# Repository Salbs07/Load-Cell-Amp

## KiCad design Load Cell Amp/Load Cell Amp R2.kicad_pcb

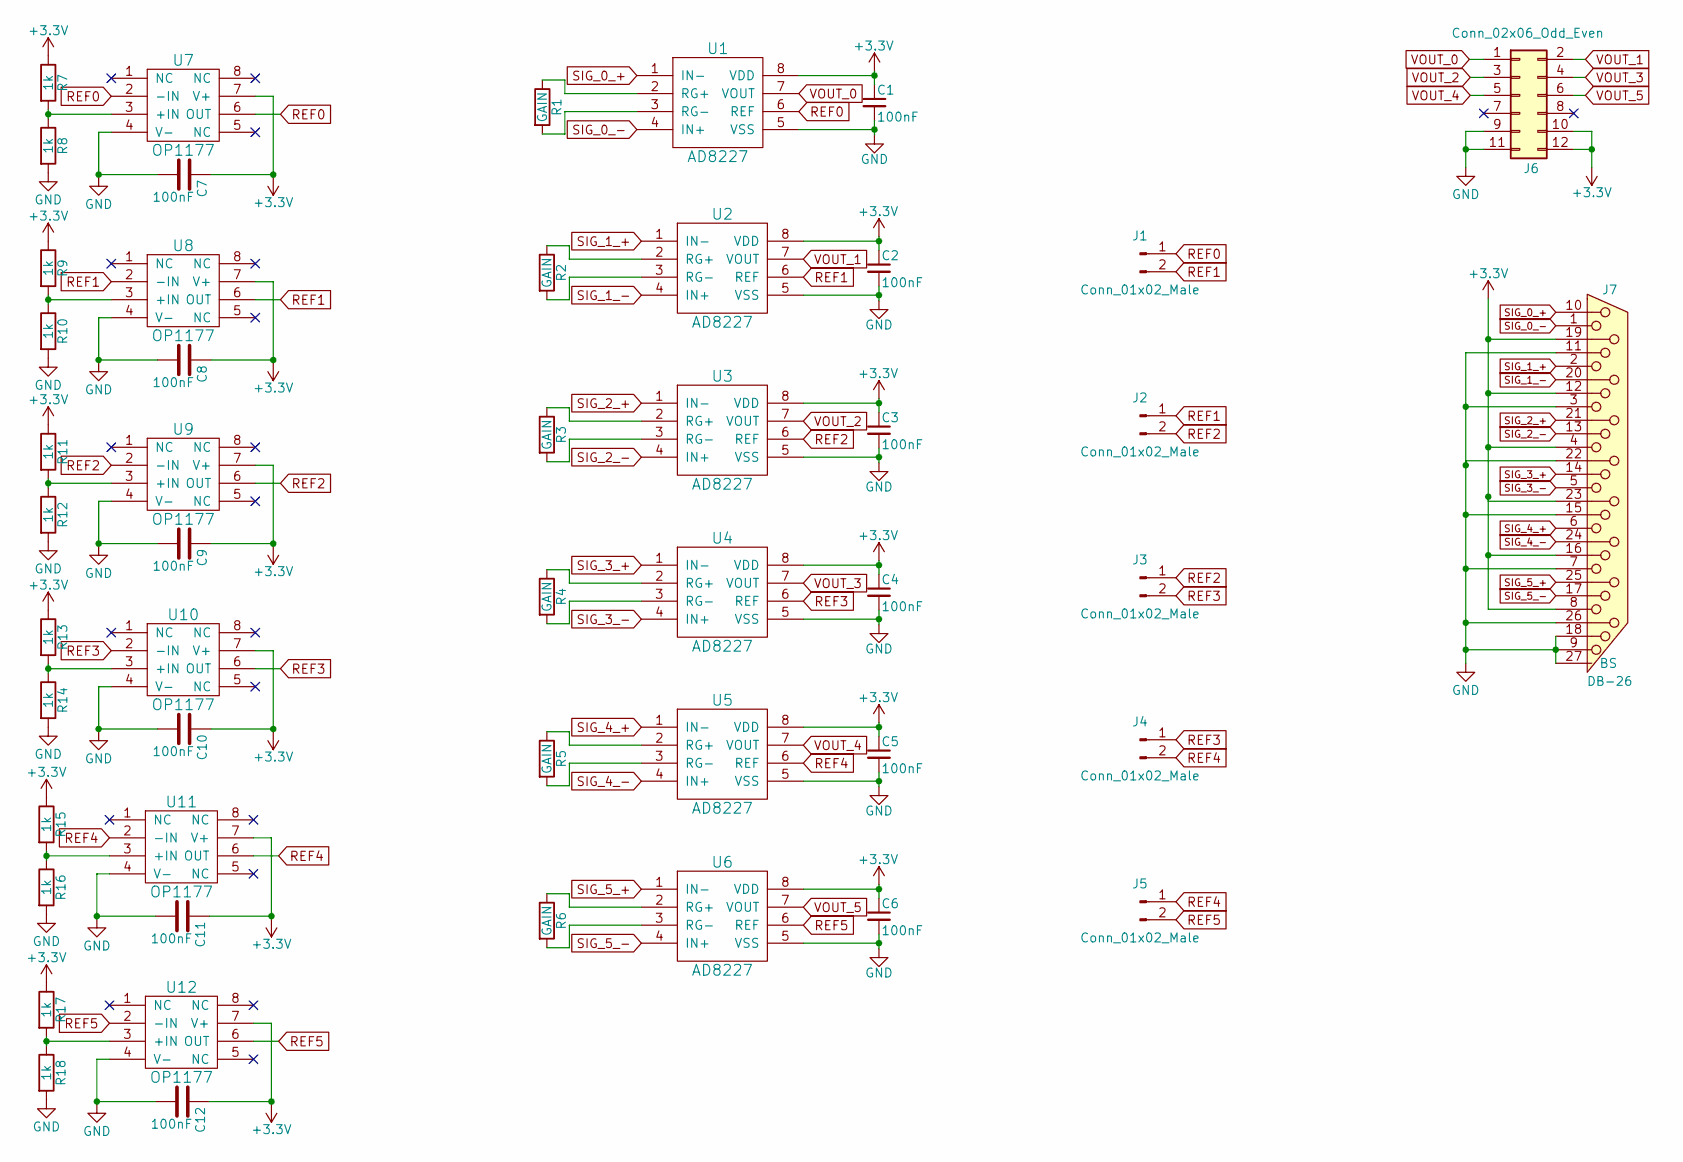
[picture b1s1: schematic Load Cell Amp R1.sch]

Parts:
C1, C2, C3, C4, C5, C6, C7, C8, C9, C10, C11, C12: 100nF; C_0805
J1, J2, J3, J4, J5: Conn_01x02_Male; Pin_Header_Straight_1x02_Pitch2.54mm
J6: Conn_02x06_Odd_Even; Pin_Header_Straight_2x06_Pitch2.54mm
J7: DB-26; DB-26_hd
R1, R2, R3, R4, R5, R6: GAIN; R_0805
R7, R8, R9, R10, R11, R12, R13, R14, R15, R16, R17, R18: 1k; R_0805
U1, U2, U3, U4, U5, U6: AD8227; SOIC-8_3.9x4.9mm_Pitch1.27mm
U7, U8, U9, U10, U11, U12: OP1177; MSOP-8_3x3mm_Pitch0.65mm

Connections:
+3V3: C1.1, C2.1, C3.1, C4.1, C5.1, C6.1, C7.1, C8.1, C9.1, C10.1, C11.1, C12.1, J6.10, J6.12, J7.4, J7.8, J7.12, J7.16, J7.19, J7.23, R7.1, R9.1, R11.1, R13.1, R15.1, R17.1, U1.8 (VDD), U2.8 (VDD), U3.8 (VDD), U4.8 (VDD), U5.8 (VDD), U6.8 (VDD), U7.7 (V+), U8.7 (V+), U9.7 (V+), U10.7 (V+), U11.7 (V+), U12.7 (V+)
GND: C1.2, C2.2, C3.2, C4.2, C5.2, C6.2, C7.2, C8.2, C9.2, C10.2, C11.2, C12.2, J6.9, J6.11, J7.3, J7.7, J7.9, J7.11, J7.15, J7.18, J7.22, J7.26, J7.27 (BS), R8.2, R10.2, R12.2, R14.2, R16.2, R18.2, U1.5 (VSS), U2.5 (VSS), U3.5 (VSS), U4.5 (VSS), U5.5 (VSS), U6.5 (VSS), U7.4 (V-), U8.4 (V-), U9.4 (V-), U10.4 (V-), U11.4 (V-), U12.4 (V-)
unnamed: R1.1, U1.2 (RG+)
unnamed: R1.2, U1.3 (RG-)
unnamed: R2.1, U2.2 (RG+)
unnamed: R2.2, U2.3 (RG-)
unnamed: R3.1, U3.2 (RG+)
unnamed: R3.2, U3.3 (RG-)
unnamed: R4.1, U4.2 (RG+)
unnamed: R4.2, U4.3 (RG-)
unnamed: R5.1, U5.2 (RG+)
unnamed: R5.2, U5.3 (RG-)
unnamed: R6.1, U6.2 (RG+)
unnamed: R6.2, U6.3 (RG-)
unnamed: R7.2, R8.1, U7.3 (+IN)
unnamed: R9.2, R10.1, U8.3 (+IN)
unnamed: R11.2, R12.1, U9.3 (+IN)
unnamed: R13.2, R14.1, U10.3 (+IN)
unnamed: R15.2, R16.1, U11.3 (+IN)
unnamed: R17.2, R18.1, U12.3 (+IN)
REF0: J1.1, U1.6 (REF), U7.2 (-IN), U7.6 (OUT)
REF1: J1.2, J2.1, U2.6 (REF), U8.2 (-IN), U8.6 (OUT)
REF2: J2.2, J3.1, U3.6 (REF), U9.2 (-IN), U9.6 (OUT)
REF3: J3.2, J4.1, U4.6 (REF), U10.2 (-IN), U10.6 (OUT)
REF4: J4.2, J5.1, U5.6 (REF), U11.2 (-IN), U11.6 (OUT)
REF5: J5.2, U6.6 (REF), U12.2 (-IN), U12.6 (OUT)
SIG_0_+: J7.10, U1.1 (IN-)
SIG_0_-: J7.1, U1.4 (IN+)
SIG_1_+: J7.2, U2.1 (IN-)
SIG_1_-: J7.20, U2.4 (IN+)
SIG_2_+: J7.21, U3.1 (IN-)
SIG_2_-: J7.13, U3.4 (IN+)
SIG_3_+: J7.14, U4.1 (IN-)
SIG_3_-: J7.5, U4.4 (IN+)
SIG_4_+: J7.6, U5.1 (IN-)
SIG_4_-: J7.24, U5.4 (IN+)
SIG_5_+: J7.25, U6.1 (IN-)
SIG_5_-: J7.17, U6.4 (IN+)
VOUT_0: J6.1, U1.7 (VOUT)
VOUT_1: J6.2, U2.7 (VOUT)
VOUT_2: J6.3, U3.7 (VOUT)
VOUT_3: J6.4, U4.7 (VOUT)
VOUT_4: J6.5, U5.7 (VOUT)
VOUT_5: J6.6, U6.7 (VOUT)

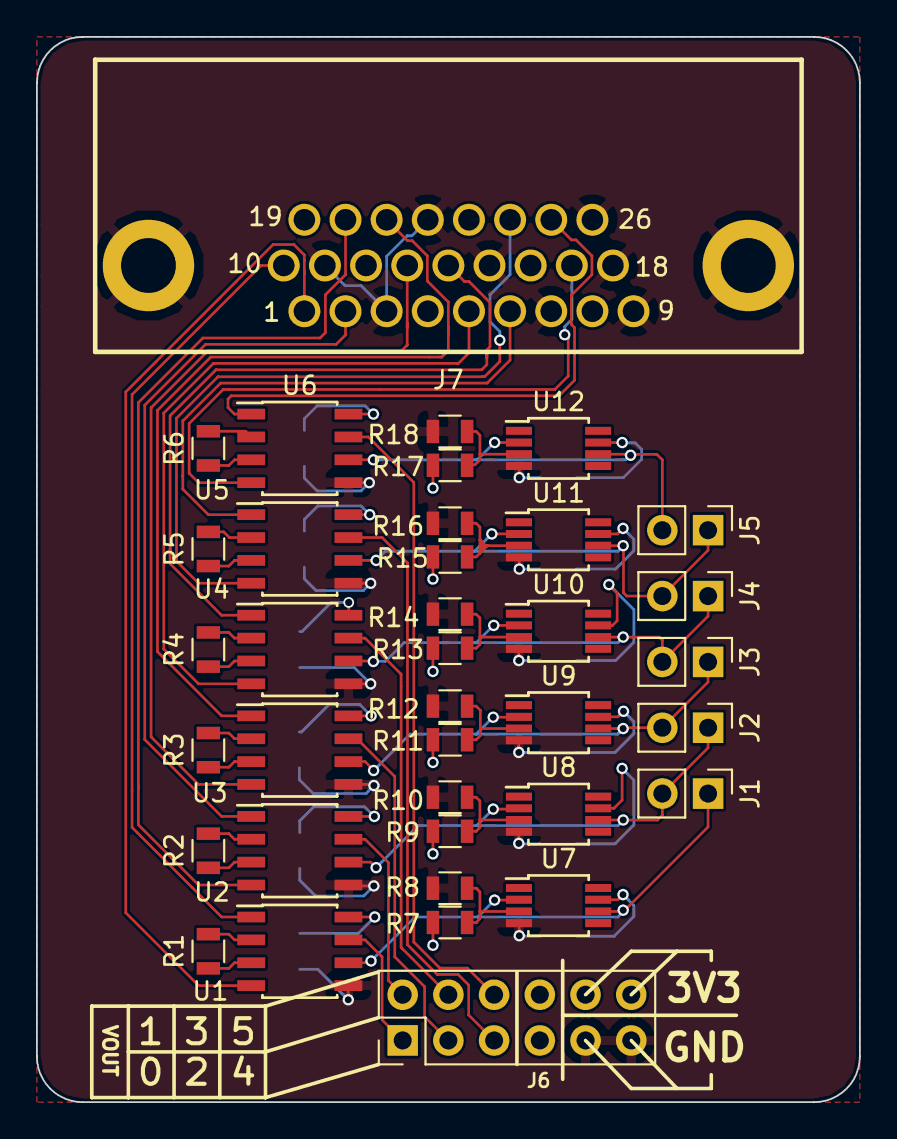
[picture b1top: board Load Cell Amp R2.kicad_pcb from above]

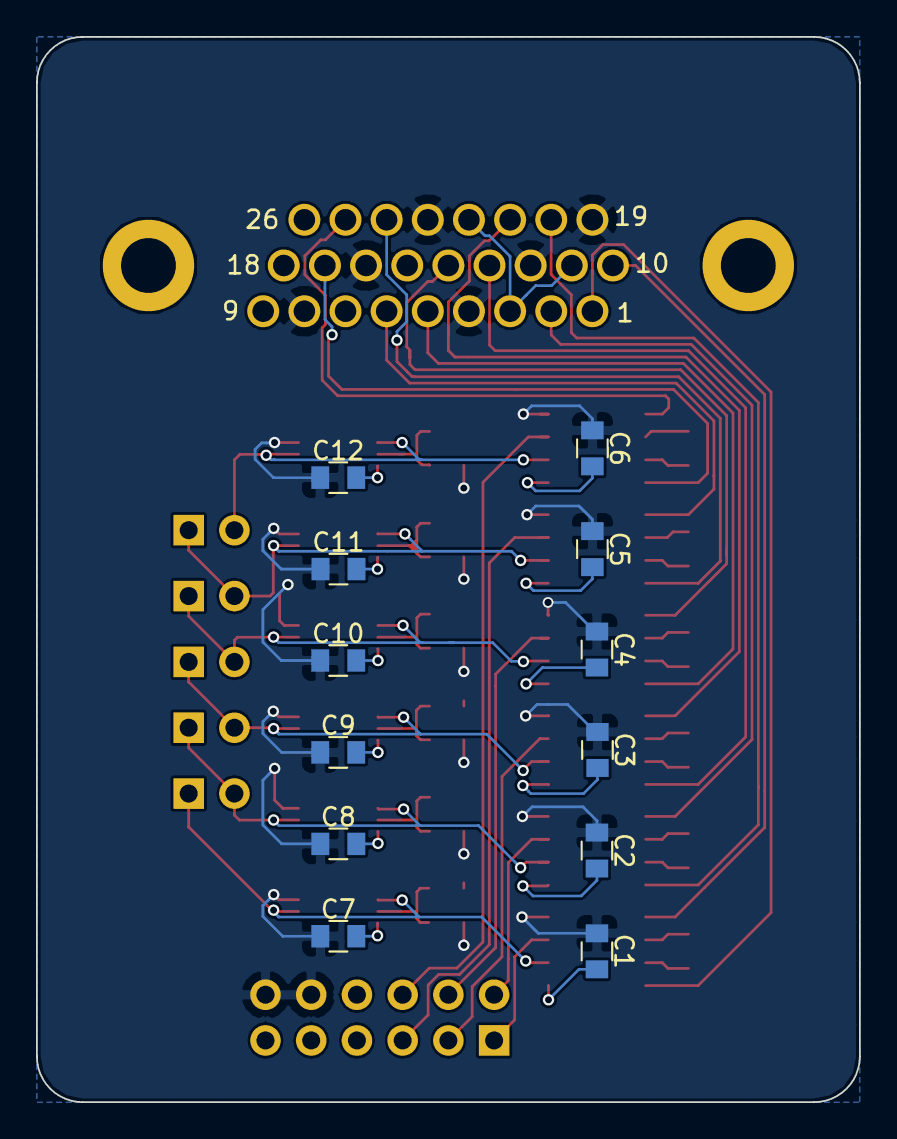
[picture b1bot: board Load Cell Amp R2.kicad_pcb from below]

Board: 2 copper layers, 45.7 x 59.2 mm, 49 parts (12 on the bottom side), 44 nets.

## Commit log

2017-11-03 initial upload
2017-11-03 edits1
2017-11-03 updates1.1
2017-11-03 edits1.2
2017-11-03 edits1.3
2017-11-03 Final changes
